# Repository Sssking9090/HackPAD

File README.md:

# MyMacropad
Hi This is my submission for Hackpad!  
This was made for Highway to Undercity.

## Features

- [x] 2x LEDS  
- [x] Rotary Encoder  
- [x] 4 keys
- [x] Hot swapable keys    
- [x] KMK firmware  

## PCB

Here are pictures of my PCB:

**Schematic**

**PCB**

**3D view**

- [x] I ran DRC and there are 0 errors ✅

## CAD

Designed using Onshape.  
Everything fits together with 4x M3 screws and nuts. I added holes for the leds.

## Firmware

Written in **Python** using **KMK**, so it’s easy to customize!  
You’ll find the code in the `main.py` file in this repo.

You can use this macropad to:
- Undo Redo 
- Volume controls 
- control pen and mouse on a whiteboard (depends on which ones but you can always change the keys)

## BOM

| Qty | Part |
|-----|------|
| 1x  | Seeeduino XIAO RP2040 |
| 4x | Cherry MX Switches |
| 2x  | SK6812-MINI-E LEDs |
| 4x  | M3 screws and matching nuts |
| 1x  | EC11 Rotary encoders |

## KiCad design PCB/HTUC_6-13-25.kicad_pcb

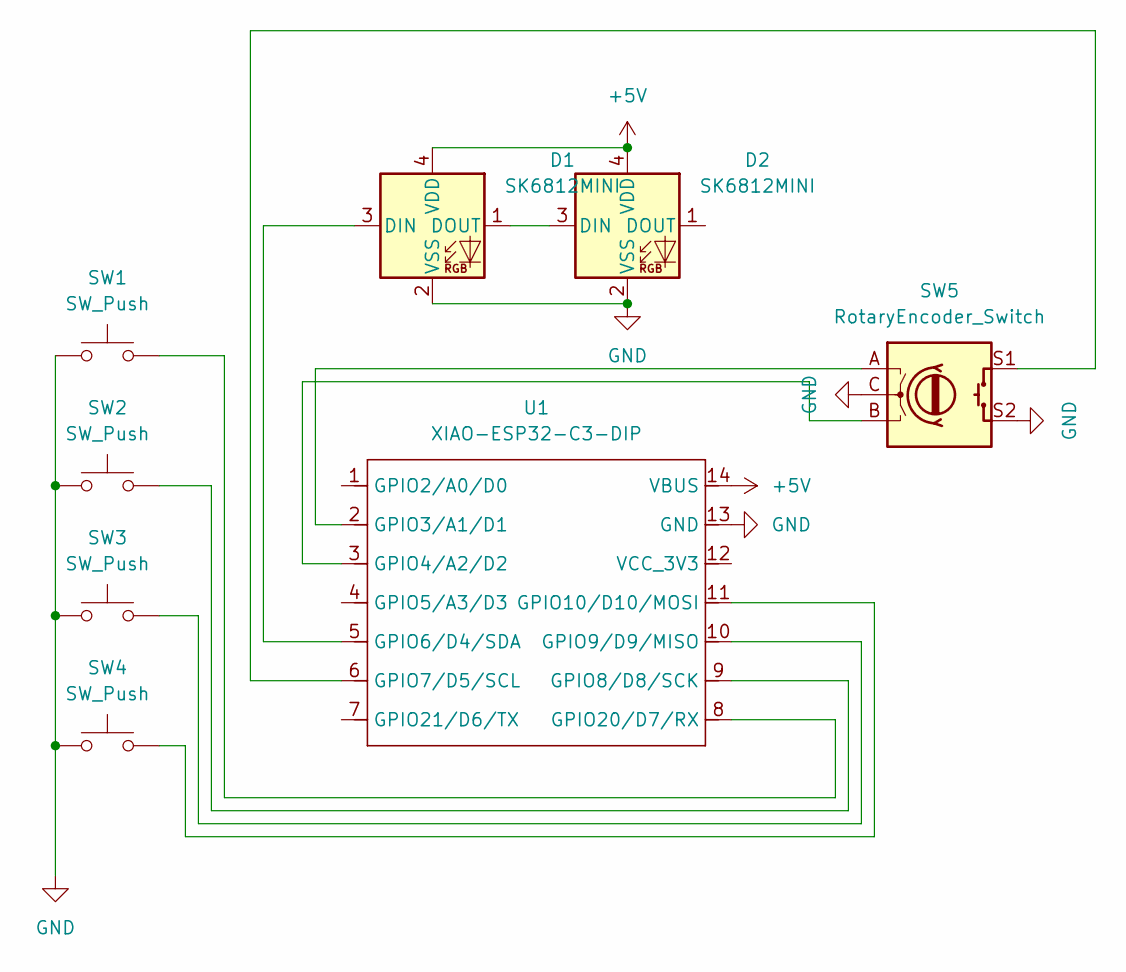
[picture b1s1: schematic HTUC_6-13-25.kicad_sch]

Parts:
D1, D2: SK6812MINI; LED_SK6812MINI_PLCC4_3.5x3.5mm_P1.75mm
SW1, SW2, SW3, SW4: SW_Push; SW_Cherry_MX_1.00u_PCB
SW5: RotaryEncoder_Switch; RotaryEncoder_Alps_EC11E-Switch_Vertical_H20mm
U1: XIAO-ESP32-C3-DIP; XIAO-RP2040-DIP

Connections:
+5V: D1.4 (VDD), D2.4 (VDD), U1.14 (VBUS)
GND: D1.2 (VSS), D2.2 (VSS), SW1.1, SW2.1, SW3.1, SW4.1, SW5.C, SW5.S2, U1.13 (GND)
unnamed: D1.3 (DIN), U1.5 (GPIO6/D4/SDA)
unnamed: D1.1 (DOUT), D2.3 (DIN)
unnamed: SW5.A, U1.2 (GPIO3/A1/D1)
unnamed: SW5.B, U1.3 (GPIO4/A2/D2)
unnamed: SW5.S1, U1.6 (GPIO7/D5/SCL)
unnamed: SW2.2, U1.9 (GPIO8/D8/SCK)
unnamed: SW3.2, U1.10 (GPIO9/D9/MISO)
unnamed: SW4.2, U1.11 (GPIO10/D10/MOSI)
unnamed: SW1.2, U1.8 (GPIO20/D7/RX)

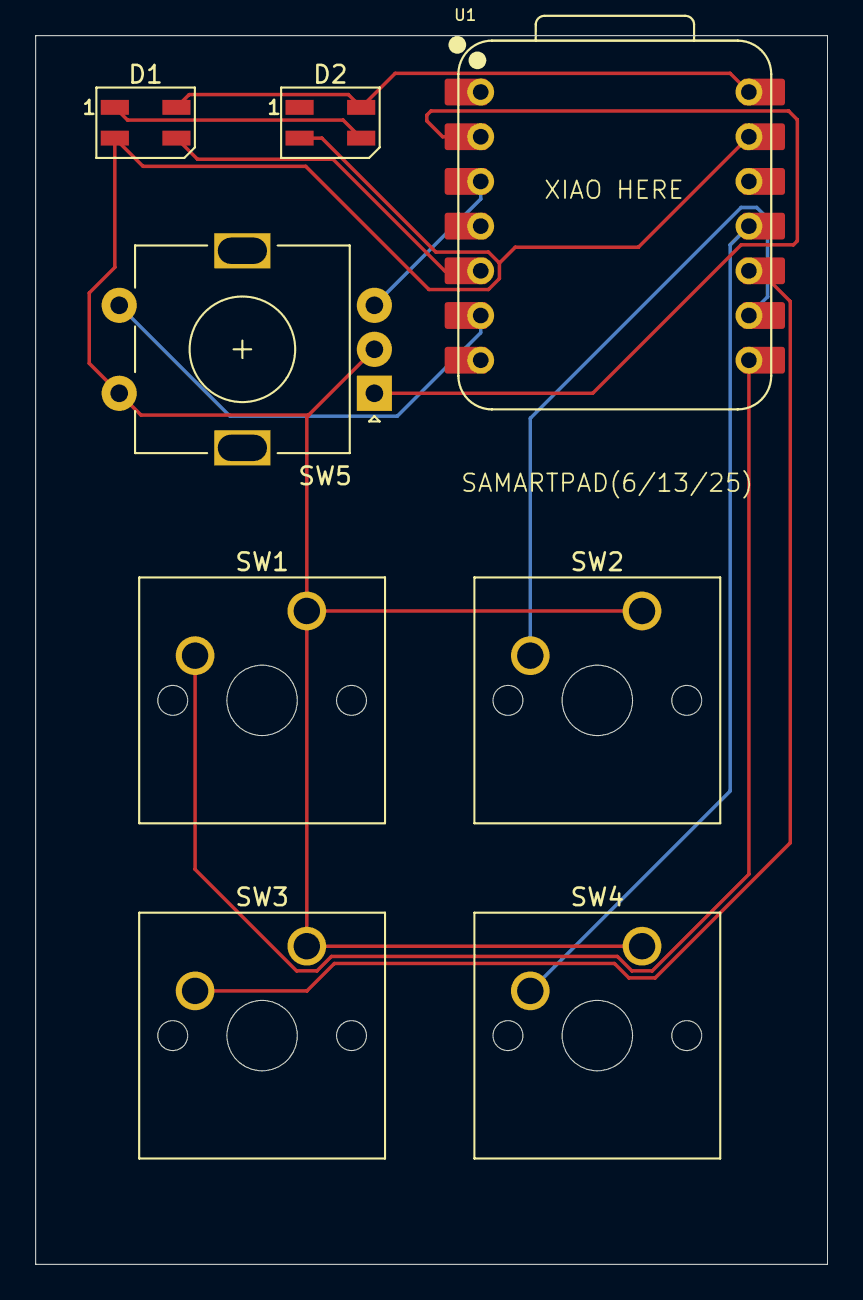
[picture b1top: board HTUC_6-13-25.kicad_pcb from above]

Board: 2 copper layers, 45.0 x 69.8 mm, 8 parts (0 on the bottom side), 11 nets.
